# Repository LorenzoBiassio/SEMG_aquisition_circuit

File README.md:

# SEMG_aquisition_circuit
 AD8232 based biosignal aquisition circuit

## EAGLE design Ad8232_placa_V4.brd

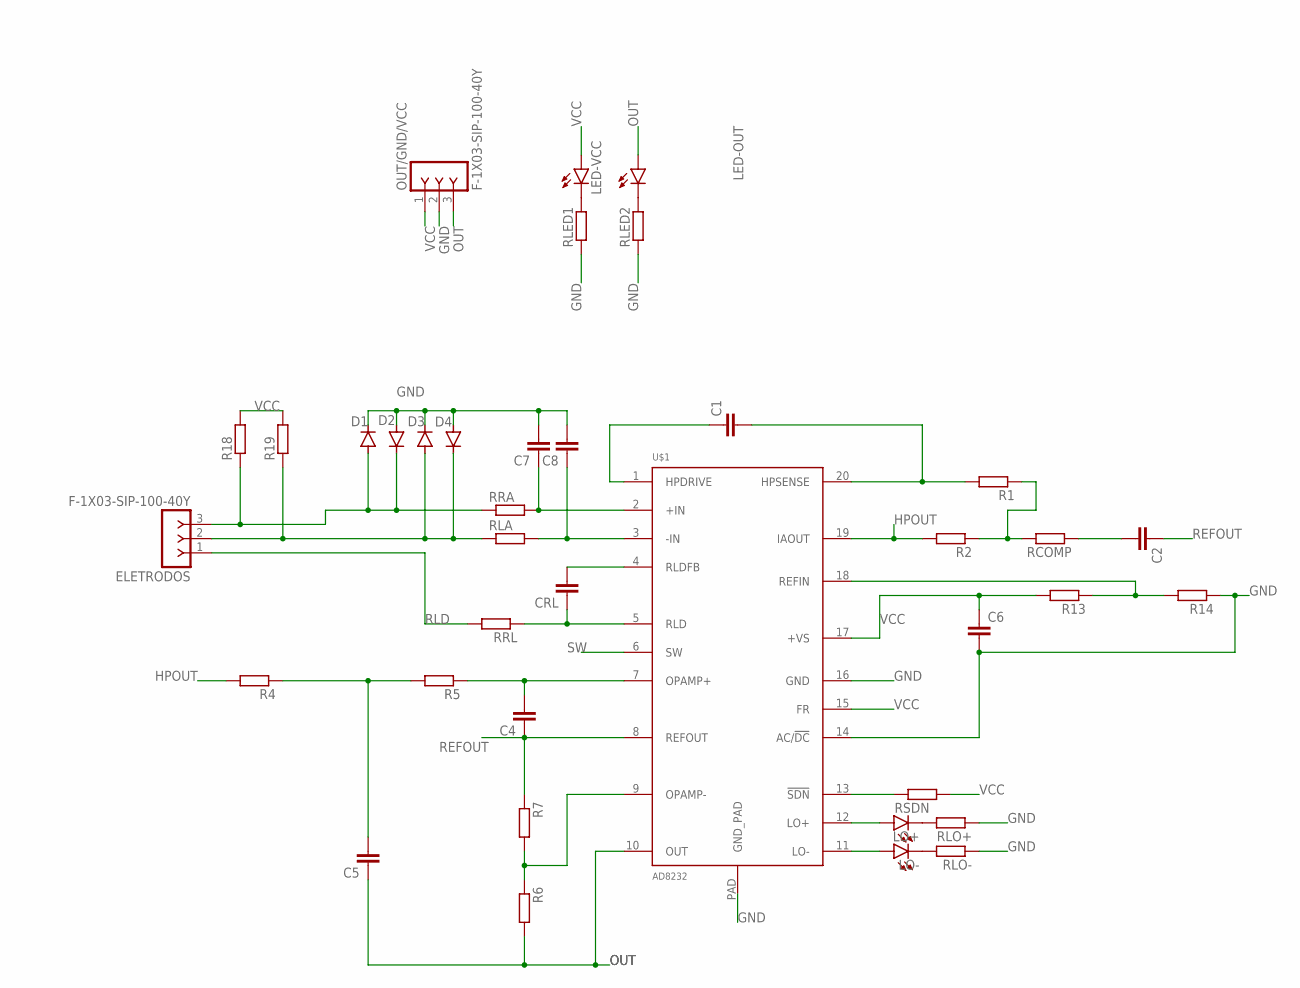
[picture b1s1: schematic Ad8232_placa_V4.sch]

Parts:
C1, C2, C4, C5, C6, C7, C8: C-EUC0805; C0805
CRL: C-EUC0805; C0805
D1, D2, D3, D4: DIODE-MINIMELF; MINIMELF
ELETRODOS: F-1X03-SIP-100-40Y; SIP-100-03-40Y
LED-OUT: LEDCHIPLED_0603; CHIPLED_0603
LED-VCC: LEDCHIPLED_0603; CHIPLED_0603
LO+: LEDCHIPLED_0603; CHIPLED_0603
LO-: LEDCHIPLED_0603; CHIPLED_0603
OUT/GND/VCC: F-1X03-SIP-100-40Y; SIP-100-03-40Y
R1, R2, R4, R5, R6, R7, R13, R14, R18, R19: R-EU_R0805; R0805
RCOMP: R-EU_R0805; R0805
RLA: R-EU_R0805; R0805
RLED1, RLED2: R-EU_R0805; R0805
RLO+: R-EU_R0805; R0805
RLO-: R-EU_R0805; R0805
RRA: R-EU_R0805; R0805
RRL: R-EU_R0805; R0805
RSDN: R-EU_R0805; R0805
U$1: AD8232; LFCSP_20

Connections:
GND: C6.2, C7.2, C8.2, D1.C, D2.A, D3.C, D4.A, OUT/GND/VCC.2, R14.1, RLED1.1, RLED2.1, RLO+.1, RLO-.1, U$1.14 (AC/!DC), U$1.16 (GND), U$1.PAD (GND_PAD)
HPOUT: R2.2, R4.2, U$1.19 (IAOUT)
LO+: LO+.A, U$1.12 (LO+)
LO-: LO-.A, U$1.11 (LO-)
unnamed: C1.1, U$1.1 (HPDRIVE)
unnamed: C1.2, R1.2, U$1.20 (HPSENSE)
unnamed: C7.1, RRA.2, U$1.2 (+IN)
unnamed: C8.1, RLA.2, U$1.3 (-IN)
unnamed: D1.A, D2.C, ELETRODOS.3, R18.1, RRA.1
unnamed: D3.A, D4.C, ELETRODOS.2, R19.1, RLA.1
unnamed: CRL.2, U$1.4 (RLDFB)
unnamed: CRL.1, RRL.1, U$1.5 (RLD)
unnamed: C4.2, R5.1, U$1.7 (OPAMP+)
unnamed: R13.1, R14.2, U$1.18 (REFIN)
unnamed: R6.1, R7.2, U$1.9 (OPAMP-)
unnamed: LED-OUT.C, RLED2.2
unnamed: R1.1, R2.1, RCOMP.2
unnamed: C5.2, R4.1, R5.2
unnamed: LED-VCC.C, RLED1.2
unnamed: RSDN.2, U$1.13 (!SDN)
unnamed: LO+.C, RLO+.2
unnamed: LO-.C, RLO-.2
OUT: C5.1, LED-OUT.A, OUT/GND/VCC.3, R6.2, U$1.10 (OUT)
REFOUT: C2.1, C4.1, R7.1, U$1.8 (REFOUT)
RLD: ELETRODOS.1, RRL.2
SW: C2.2, RCOMP.1, U$1.6 (SW)
VCC: C6.1, LED-VCC.A, OUT/GND/VCC.1, R13.2, R18.2, R19.2, RSDN.1, U$1.15 (FR), U$1.17 (+VS)

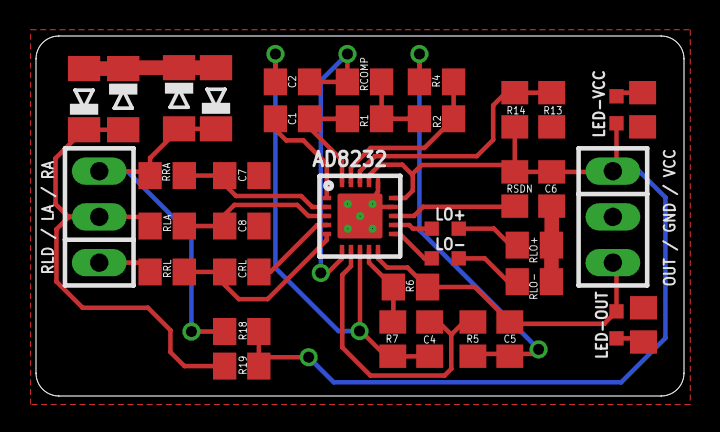
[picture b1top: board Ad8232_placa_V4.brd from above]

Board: 2 copper layers, 36.0 x 20.0 mm, 38 parts (0 on the bottom side), 27 nets.

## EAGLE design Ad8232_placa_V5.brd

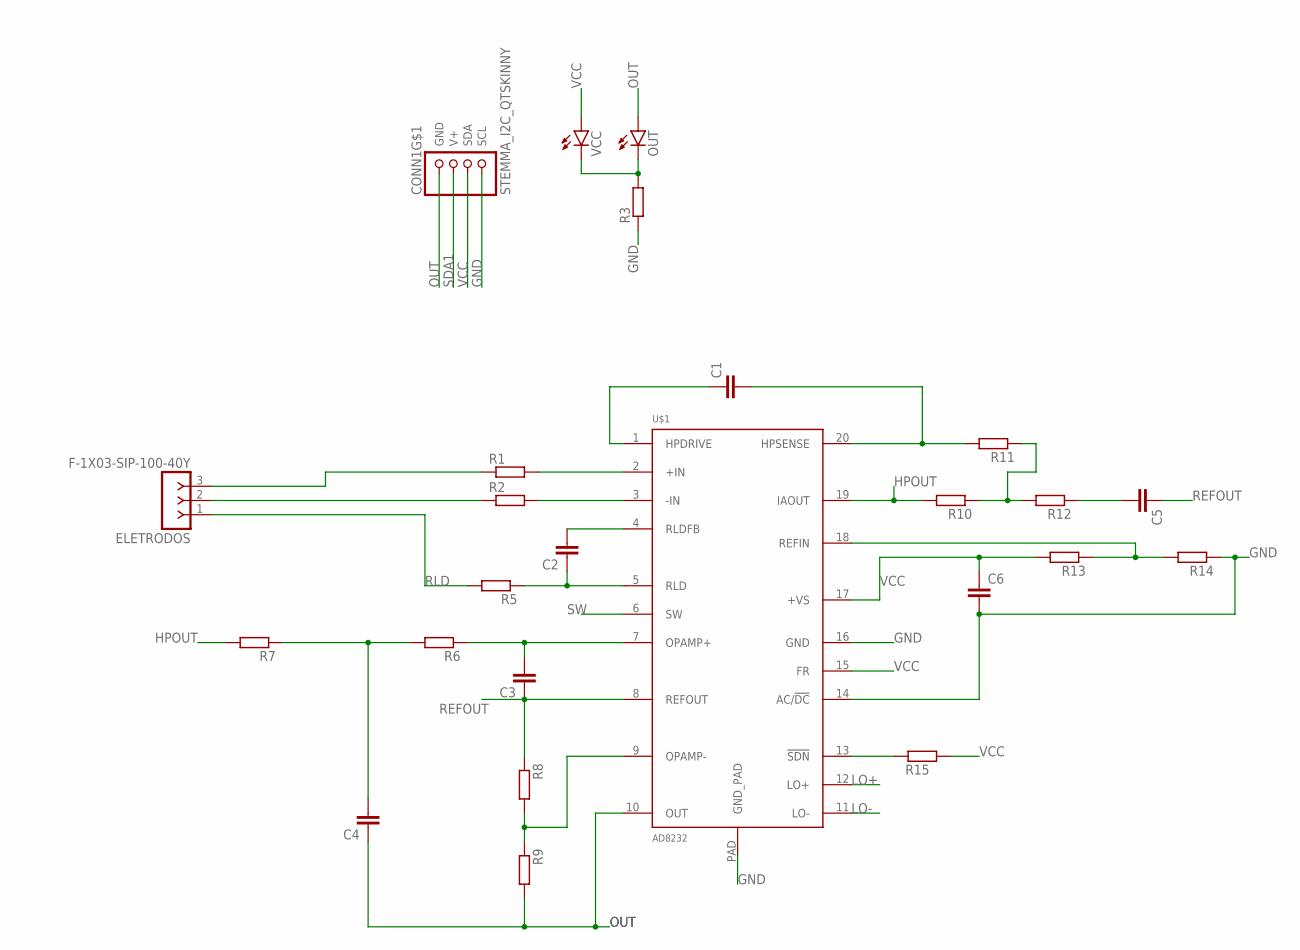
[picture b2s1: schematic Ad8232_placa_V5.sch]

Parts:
C1, C2, C3, C4, C5, C6: C-EUC0402K; C0402K
CONN1: STEMMA_I2C_QTSKINNY; JST_SH4_SKINNY
ELETRODOS: F-1X03-SIP-100-40Y; SIP-100-03-40Y
OUT: LEDCHIPLED_0603; CHIPLED_0603
R1, R2, R3, R5, R6, R7, R8, R9, R10, R11, R12, R13, R14, R15: R-EU_R0402; R0402
U$1: AD8232; LFCSP_20
VCC: LEDCHIPLED_0603; CHIPLED_0603

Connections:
GND: C6.2, CONN1.4 (SCL), R3.1, R14.1, U$1.14 (AC/!DC), U$1.16 (GND), U$1.PAD (GND_PAD)
HPOUT: R7.2, R10.2, U$1.19 (IAOUT)
LO+: U$1.12 (LO+)
LO-: U$1.11 (LO-)
unnamed: C1.1, U$1.1 (HPDRIVE)
unnamed: C1.2, R11.2, U$1.20 (HPSENSE)
unnamed: R1.2, U$1.2 (+IN)
unnamed: R2.2, U$1.3 (-IN)
unnamed: ELETRODOS.3, R1.1
unnamed: ELETRODOS.2, R2.1
unnamed: C2.2, U$1.4 (RLDFB)
unnamed: C2.1, R5.1, U$1.5 (RLD)
unnamed: C3.2, R6.1, U$1.7 (OPAMP+)
unnamed: R13.1, R14.2, U$1.18 (REFIN)
unnamed: R8.2, R9.1, U$1.9 (OPAMP-)
unnamed: OUT.C, R3.2, VCC.C
unnamed: R10.1, R11.1, R12.2
unnamed: C4.2, R6.2, R7.1
unnamed: R15.2, U$1.13 (!SDN)
OUT: C4.1, CONN1.1 (GND), OUT.A, R9.2, U$1.10 (OUT)
REFOUT: C3.1, C5.1, R8.1, U$1.8 (REFOUT)
RLD: ELETRODOS.1, R5.2
SDA1: CONN1.2 (V+)
SW: C5.2, R12.1, U$1.6 (SW)
VCC: C6.1, CONN1.3 (SDA), R13.2, R15.1, U$1.15 (FR), U$1.17 (+VS), VCC.A

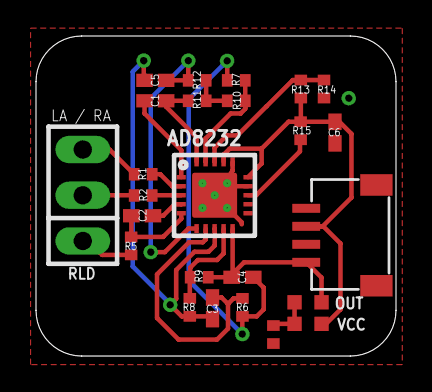
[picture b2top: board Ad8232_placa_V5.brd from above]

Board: 2 copper layers, 20.0 x 17.8 mm, 25 parts (0 on the bottom side), 22 nets.

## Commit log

2022-12-22 Circuits developed for the last year
    All the CAD files are for Autodesk Eagle and were developed inside UTFPR for research purposes

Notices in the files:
parts and their libraries:
con-headers-jp: Copyright (C) 2008, Bob Starr
microbuilder: This work is placed in the public domain, and may be freely used for commercial and non-commercial work with the following conditions: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
